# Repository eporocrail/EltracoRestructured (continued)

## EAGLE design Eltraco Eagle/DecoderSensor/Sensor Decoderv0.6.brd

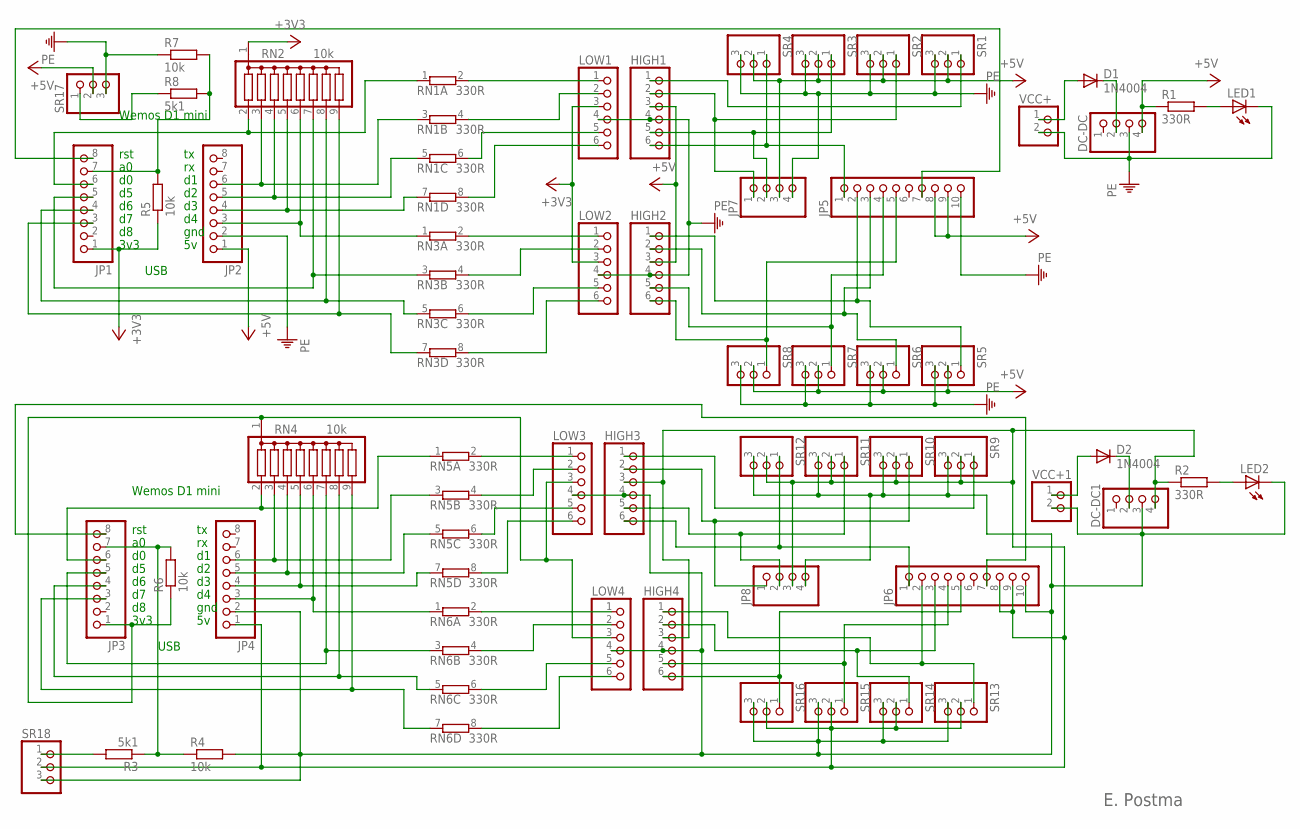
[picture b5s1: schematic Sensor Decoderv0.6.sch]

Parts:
D1, D2: 1N4004; DO41-10
DC-DC, DC-DC1: PINHD-1X4; 1X04
HIGH1, HIGH2, HIGH3, HIGH4: PINHD-1X6; 1X06
JP1, JP2, JP3, JP4: PINHD-1X8; 1X08
JP5, JP6: PINHD-1X10; 1X10
JP7, JP8: PINHD-1X4; 1X04
LED1, LED2: LED3MM
LOW1, LOW2, LOW3, LOW4: PINHD-1X6; 1X06
R1, R2: 330R; 0207/7
R3, R8: 5k1; 0207/7
R4, R5, R6, R7: 10k; 0207/7
RN1, RN3, RN5, RN6: 330R; SIL8
RN2, RN4: 10k; SIL9
SR1, SR2, SR3, SR4, SR5, SR6, SR7, SR8, SR9, SR10, SR11, SR12, SR13, SR14, SR15, SR16, SR17, SR18: PINHD-1X3; 1X03
VCC+, VCC+1: PINHD-1X2; 1X02

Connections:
+3V3: JP1.1, LOW1.3, LOW2.3, R5.1, RN2.1
+5V: DC-DC.4, HIGH1.3, HIGH2.3, JP2.1, JP5.8, JP5.9, JP7.3, R1.1, SR1.2, SR2.2, SR3.2, SR4.2, SR5.2, SR6.2, SR7.2, SR8.2, SR17.2
unnamed: HIGH2.6, JP5.5, SR8.1
unnamed: JP1.6, RN1.1, RN2.2
unnamed: JP1.4, RN2.8, RN3.5 (1)
unnamed: D1.C, DC-DC.2
unnamed: JP1.5, RN2.7, RN3.3 (1)
unnamed: LED1.A, R1.2
unnamed: JP2.5, RN1.5 (1), RN2.4
unnamed: HIGH2.5, JP5.4, SR7.1
unnamed: JP2.3, RN2.6, RN3.1
unnamed: JP2.6, RN1.3 (1), RN2.3
unnamed: JP1.3, RN2.9, RN3.7 (1)
unnamed: LOW1.1, RN1.2
unnamed: JP2.4, RN1.7 (1), RN2.5
unnamed: HIGH1.5, JP7.2, SR3.1
unnamed: HIGH1.1, SR1.1
unnamed: HIGH1.6, JP5.1, SR4.1
unnamed: HIGH1.2, JP7.1, SR2.1
unnamed: HIGH2.2, JP5.3, SR6.1
unnamed: HIGH2.1, JP5.2, SR5.1
unnamed: JP3.6, RN4.2, RN5.1
unnamed: LED2.A, R2.2
unnamed: JP4.6, RN4.3, RN5.3 (1)
unnamed: JP4.5, RN4.4, RN5.5 (1)
unnamed: JP4.4, RN4.5, RN5.7 (1)
unnamed: D2.A, VCC+1.1
unnamed: D2.C, DC-DC1.2
unnamed: JP4.3, RN4.6, RN6.1
unnamed: JP3.5, RN4.7, RN6.3 (1)
unnamed: JP3.4, RN4.8, RN6.5 (1)
unnamed: JP3.3, RN4.9, RN6.7 (1)
unnamed: LOW3.1, RN5.2
unnamed: LOW3.2, RN5.4 (2)
unnamed: LOW3.5, RN5.6 (2)
unnamed: LOW3.6, RN5.8 (2)
unnamed: LOW4.1, RN6.2
unnamed: LOW4.2, RN6.4 (2)
unnamed: LOW4.5, RN6.6 (2)
unnamed: LOW4.6, RN6.8 (2)
unnamed: HIGH4.6, JP6.5, SR16.1
unnamed: HIGH4.5, JP6.4, SR15.1
unnamed: DC-DC1.3, HIGH3.4, HIGH4.4, JP4.2, JP6.10, JP8.4, LED2.K (C), LOW3.4, LOW4.4, R4.2, SR9.3, SR10.3, SR11.3, SR12.3, SR13.3, SR14.3, SR15.3, SR16.3, SR18.3, VCC+1.2
unnamed: JP3.8, JP6.7
unnamed: JP1.8, JP5.7
unnamed: LOW1.2, RN1.4 (2)
unnamed: LOW1.5, RN1.6 (2)
unnamed: LOW1.6, RN1.8 (2)
unnamed: D1.A, VCC+.1
unnamed: LOW2.1, RN3.2
unnamed: LOW2.2, RN3.4 (2)
unnamed: LOW2.5, RN3.6 (2)
unnamed: LOW2.6, RN3.8 (2)
unnamed: DC-DC1.4, HIGH3.3, HIGH4.3, JP4.1, JP6.8, JP6.9, JP8.3, R2.1, SR9.2, SR10.2, SR11.2, SR12.2, SR13.2, SR14.2, SR15.2, SR16.2, SR18.2
unnamed: HIGH3.1, SR9.1
unnamed: JP3.1, LOW3.3, LOW4.3, R6.1, RN4.1
unnamed: JP1.7, R5.2, R7.2, R8.2
unnamed: JP3.7, R3.1, R4.1, R6.2
unnamed: R3.2, SR18.1
unnamed: HIGH3.2, JP8.1, SR10.1
unnamed: R8.1, SR17.1
unnamed: HIGH3.5, JP8.2, SR11.1
unnamed: HIGH3.6, JP6.1, SR12.1
unnamed: HIGH4.2, JP6.3, SR14.1
unnamed: HIGH4.1, JP6.2, SR13.1
PE: DC-DC.3, HIGH1.4, HIGH2.4, JP2.2, JP5.10, JP7.4, LED1.K (C), LOW1.4, LOW2.4, R7.1, SR1.3, SR2.3, SR3.3, SR4.3, SR5.3, SR6.3, SR7.3, SR8.3, SR17.3, VCC+.2

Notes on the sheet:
rst
3v3
Wemos D1 mini
gnd
USB
E. Postma

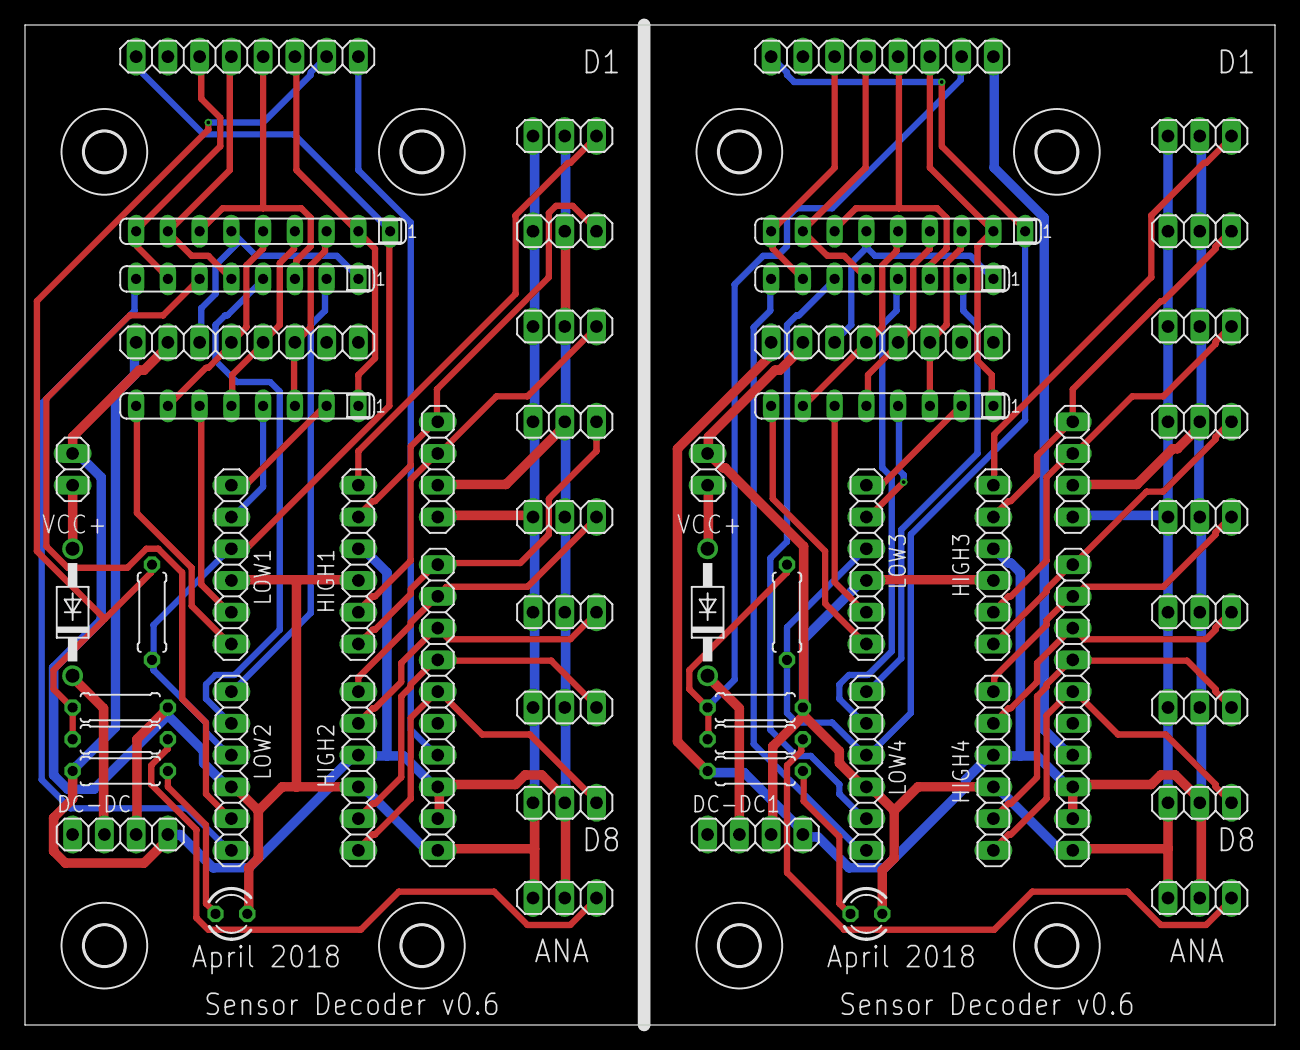
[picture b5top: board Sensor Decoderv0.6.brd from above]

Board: 2 copper layers, 100.0 x 80.0 mm, 64 parts (0 on the bottom side), 66 nets.

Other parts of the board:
U$1, U$2, U$3, U$4, U$5, U$6, U$7, U$8: 3,2

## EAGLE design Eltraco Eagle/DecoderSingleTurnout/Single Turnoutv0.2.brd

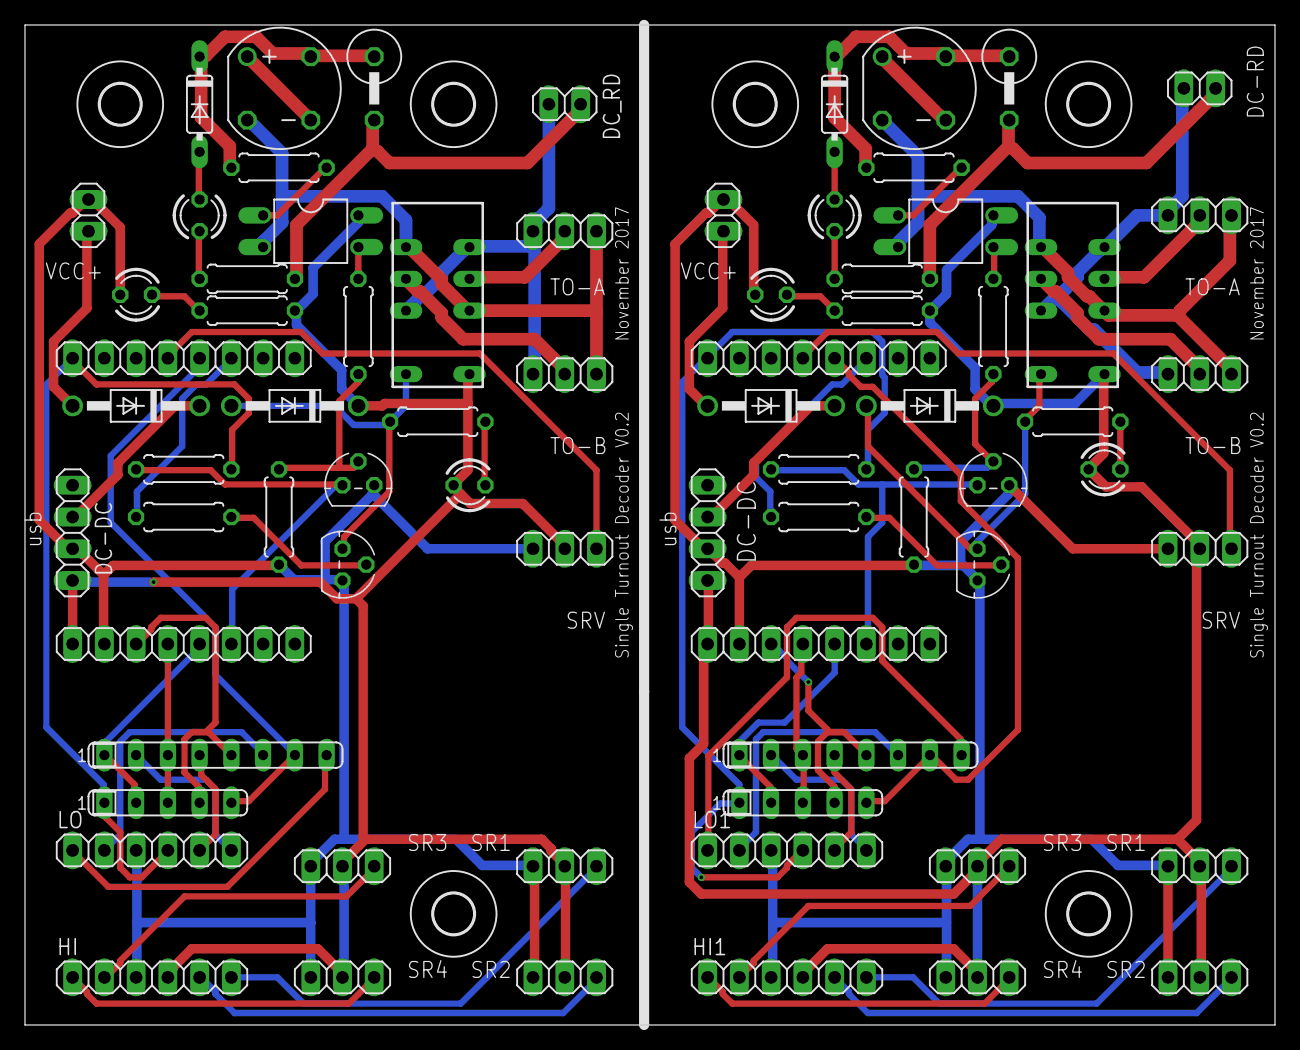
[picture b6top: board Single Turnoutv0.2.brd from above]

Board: 2 copper layers, 100.0 x 80.0 mm, 78 parts (0 on the bottom side), 72 nets.

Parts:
B1, B2: RECTIFIER-RB1A; RB1A
D1, D2, D3, D8: 1N4004; DO41-10
D4, D7: 1N4148DO35-7; DO35-7
DC-DC, DC-DC1: 1X04
DC_RD, DC_RD1: 1X02
FUSE, FUSE1: PFRA050; 0414V
HI, HI1: 1X06
JP1, JP2, JP3, JP4, JP5, JP6, JP7, JP8: 1X03
K1, K2: NA
L5V, L5V1: LED3MM
LO, LO1: 1X06
LREL, LREL1: LED3MM
LSHORT, LSHORT1: LED3MM
OK1, OK2: PC814; DIL04
R1, R2, R5, R26: 330R; 0207/7
R3, R19: 10k; 0207/7
R6, R8: 33R; 0207/7
R7, R11: 2k2; 0207/7
R9, R17: 1k; 0207/7
R10, R20: 3k3; 0207/7
R18, R21: 22k; 0207/7
RN1, RN3: 330R; SIL8
RN2, RN4: 10k; SIL5
SRV, SRV1: 1X03
T1, T2, T3, T4: BC547; TO92
TO-A, TO-A1: 1X03
TO-B, TO-B1: 1X03
U$1, U$2, U$4, U$5, U$6, U$9: 3,2
VCC+, VCC+1: 1X02
WA, WA1: 1X08
WB, WB1: 1X08

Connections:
+5V/1: D3.C, DC-DC.4, HI.4, JP1.2, JP2.2, JP3.2, JP4.2, K1.1, LREL.A, OK2.4, R1.1, SRV.2, WB.1
+5V/2: D2.C, DC-DC1.4, HI1.4, JP5.2, JP6.2, JP7.2, JP8.2, K2.1, LREL1.A, OK1.4, R26.1, SRV1.2, WB1.1
GND1: DC-DC.3, HI.3, JP1.3, JP2.3, JP3.3, JP4.3, L5V.K, LO.3, R21.2, SRV.3, T1.1, T4.1, VCC+.2, WB.2
GND2: DC-DC1.3, HI1.3, JP5.3, JP6.3, JP7.3, JP8.3, L5V1.K, LO1.3, R18.2, SRV1.3, T2.1, T3.1, VCC+1.2, WB1.2
unnamed: LO.4, R3.2, RN2.1, WA.1
unnamed: LO.6, RN1.2
unnamed: DC_RD.1, FUSE.2, R11.1
unnamed: D1.A, VCC+.1
unnamed: R3.1, T4.3, WB.6
unnamed: LREL1.K, R5.2
unnamed: OK1.1, R6.2
unnamed: LSHORT1.A, R7.2
unnamed: D4.A, LSHORT1.K
unnamed: D2.A, K2.12, R5.1, T2.3
unnamed: R9.1, T2.2
unnamed: LREL.K, R2.2
unnamed: B1.+, B1.-
unnamed: B2.AC2, K1.3, K1.8, OK2.2, TO-A.1, TO-B.1
unnamed: K2.4, TO-A1.2
unnamed: DC_RD.2, K1.5, K1.10, TO-A.3, TO-B.3
unnamed: OK2.3, R20.2
unnamed: K2.9, TO-B1.2
unnamed: B1.AC2, K2.3, K2.8, OK1.2, TO-A1.1, TO-B1.1
unnamed: B1.AC1, D4.C, FUSE1.1, R6.1
unnamed: OK2.1, R8.2
unnamed: DC_RD1.2, K2.5, K2.10, TO-A1.3, TO-B1.3
unnamed: B2.AC1, D7.C, FUSE.1, R8.1
unnamed: LO.5, RN1.4
unnamed: HI.2, JP3.1
unnamed: K1.4, TO-A.2
unnamed: DC_RD1.1, FUSE1.2, R7.1
unnamed: R20.1, R21.1, T4.2
unnamed: R17.2, WA.6
unnamed: HI.5, JP2.1
unnamed: SRV.1, WA.4
unnamed: K1.9, TO-B.2
unnamed: SRV1.1, WA1.4
unnamed: R10.1, R18.1, T3.2
unnamed: LSHORT.A, R11.2
unnamed: HI.6, JP1.1
unnamed: RN1.3, RN2.3, WB.4
unnamed: RN1.1, RN2.2, WB.5
unnamed: HI1.2, JP7.1
unnamed: HI1.5, JP6.1
unnamed: D7.A, LSHORT.K
unnamed: B2.+, B2.-
unnamed: HI1.6, JP5.1
unnamed: RN1.5, RN2.4, WB.3
unnamed: RN1.7, RN2.5, WA.5
unnamed: L5V.A, R1.2
unnamed: RN3.5, RN4.4, WB1.3
unnamed: LO1.4, R19.2, RN4.1, WA1.1
unnamed: R17.1, T1.2
unnamed: D3.A, K1.12, R2.1, T1.3
unnamed: RN3.7, RN4.5, WA1.5
unnamed: HI1.1, JP8.1
unnamed: LO.2, RN1.6
unnamed: RN3.3, RN4.3, WB1.4
unnamed: RN3.1, RN4.2, WB1.5
unnamed: LO.1, RN1.8
unnamed: LO1.6, RN3.2
unnamed: D1.C, DC-DC.2
unnamed: LO1.5, RN3.4
unnamed: LO1.2, RN3.6
unnamed: HI.1, JP4.1
unnamed: R9.2, WA1.6
unnamed: OK1.3, R10.2
unnamed: L5V1.A, R26.2
unnamed: R19.1, T3.3, WB1.6
unnamed: LO1.1, RN3.8
unnamed: D8.A, VCC+1.1
unnamed: D8.C, DC-DC1.2
